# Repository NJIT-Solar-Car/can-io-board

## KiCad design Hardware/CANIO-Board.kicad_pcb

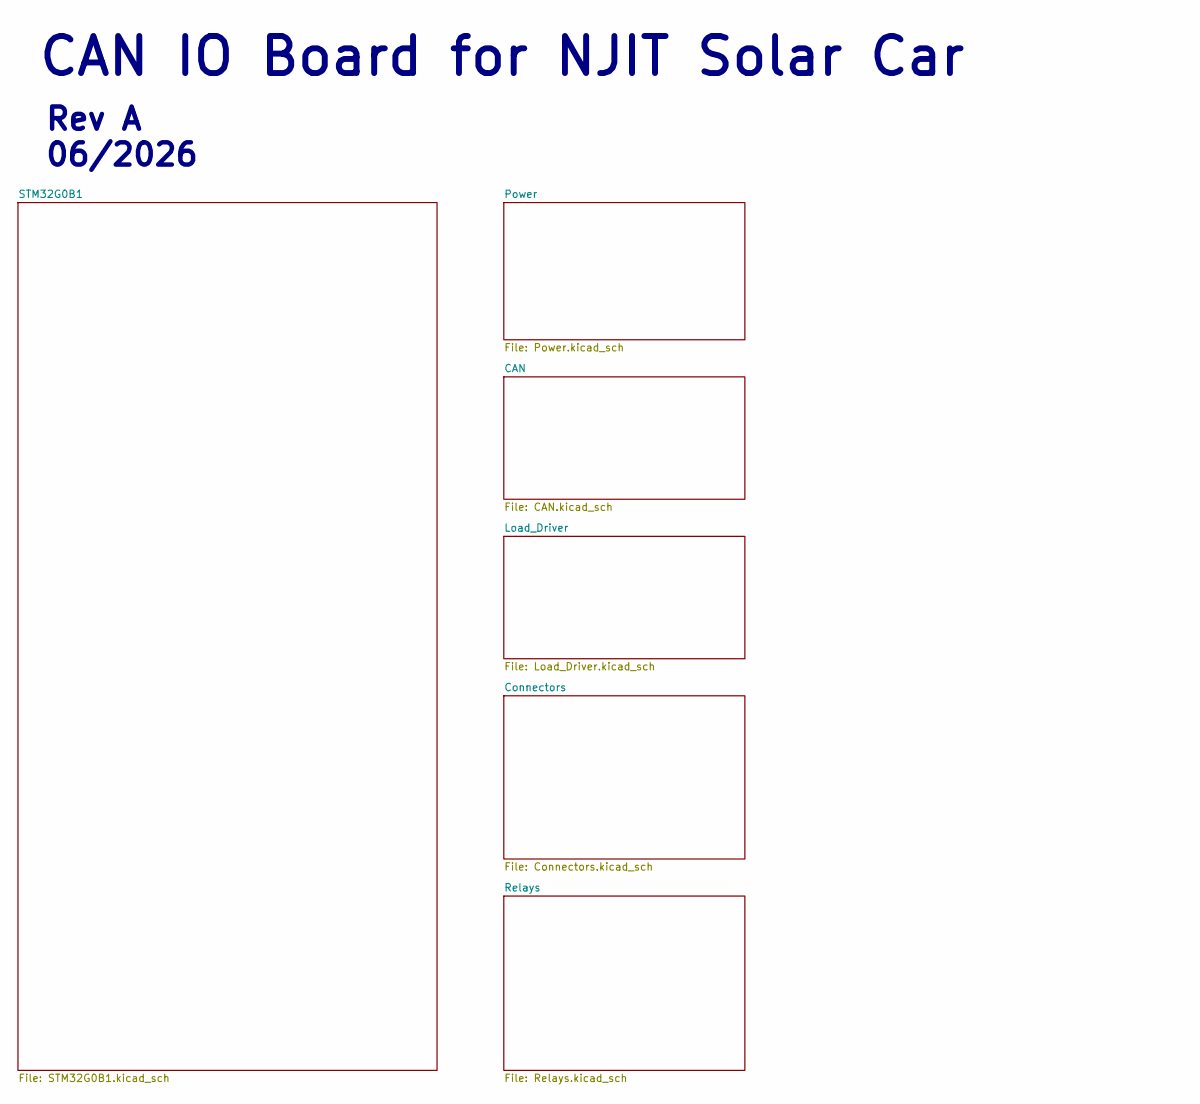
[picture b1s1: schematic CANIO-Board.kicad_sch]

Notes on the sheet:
CAN IO Board for NJIT Solar Car
Rev A 06/2026

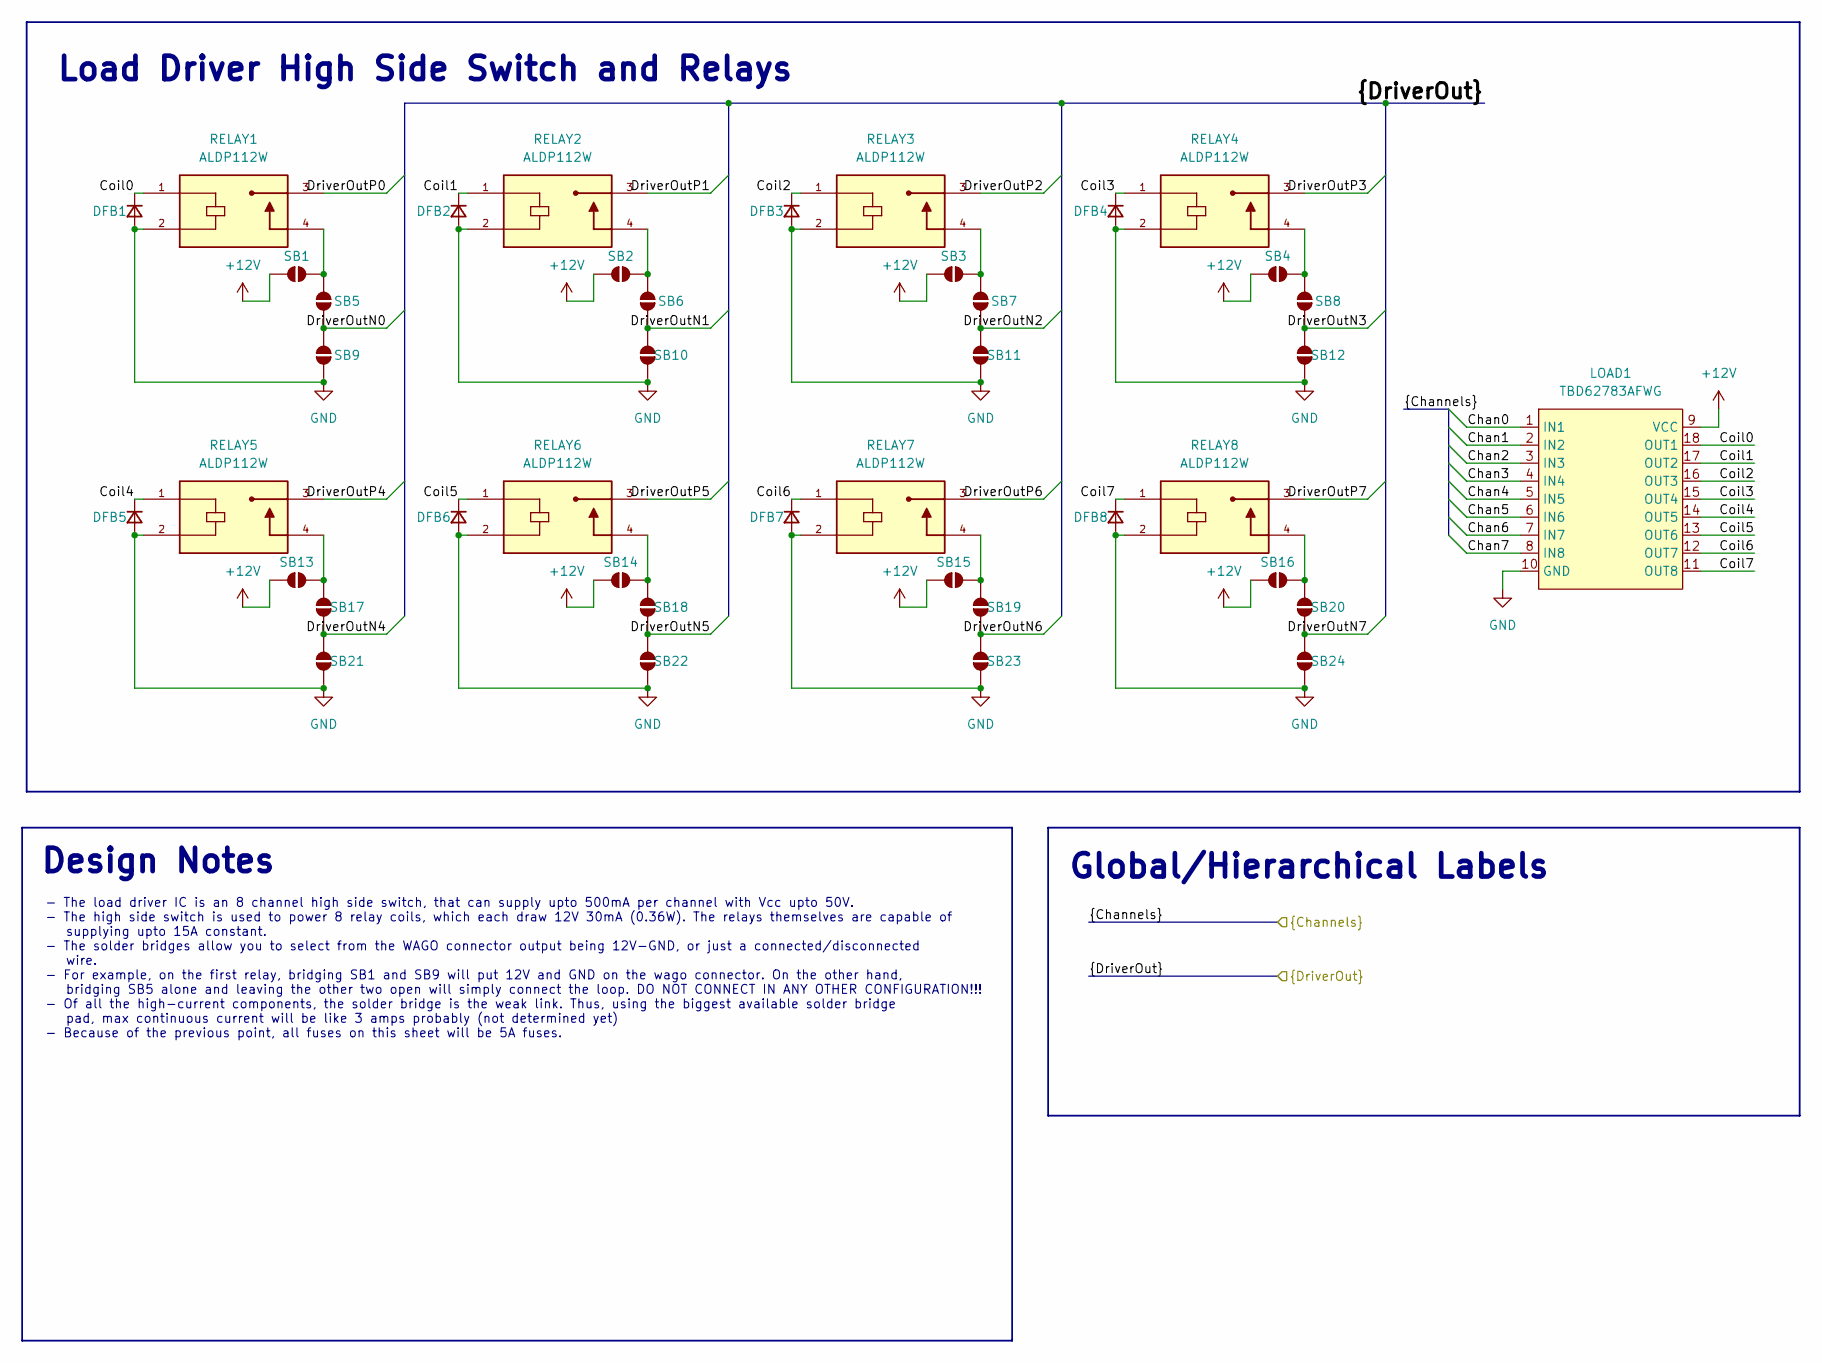
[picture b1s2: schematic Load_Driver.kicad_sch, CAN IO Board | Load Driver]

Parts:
DFB1, DFB2, DFB3, DFB4, DFB5, DFB6, DFB7, DFB8: D_Small; D_DO-35_SOD27_P7.62mm_Horizontal
LOAD1: TBD62783AFWG; SOP-18_7x12.5mm_P1.27mm
RELAY1, RELAY2, RELAY3, RELAY4, RELAY5, RELAY6, RELAY7, RELAY8: ALDP112W; RELAY_ALDP112W; PARTREV 2024.10
SB1, SB2, SB3, SB4, SB5, SB6, SB7, SB8, SB9, SB10, SB11, SB12, SB13, SB14, SB15, SB16, SB17, SB18, SB19, SB20, SB21, SB22, SB23, SB24: SolderJumper_2_Open; SolderJumper-2_P1.3mm_Open_TrianglePad1.0x1.5mm

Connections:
+12V: LOAD1.9 (VCC), SB1.1 (A), SB2.1 (A), SB3.1 (A), SB4.1 (A), SB13.1 (A), SB14.1 (A), SB15.1 (A), SB16.1 (A); also elsewhere on the board
/Connectors/DriverOutN0: SB5.2 (B), SB9.1 (A); also elsewhere on the board
/Connectors/DriverOutN1: SB6.2 (B), SB10.1 (A); also elsewhere on the board
/Connectors/DriverOutN2: SB7.2 (B), SB11.1 (A); also elsewhere on the board
/Connectors/DriverOutN3: SB8.2 (B), SB12.1 (A); also elsewhere on the board
/Connectors/DriverOutN4: SB17.2 (B), SB21.1 (A); also elsewhere on the board
/Connectors/DriverOutN5: SB18.2 (B), SB22.1 (A); also elsewhere on the board
/Connectors/DriverOutN6: SB19.2 (B), SB23.1 (A); also elsewhere on the board
/Connectors/DriverOutN7: SB20.2 (B), SB24.1 (A); also elsewhere on the board
/Connectors/DriverOutP0: RELAY1.3; also elsewhere on the board
/Connectors/DriverOutP1: RELAY2.3; also elsewhere on the board
/Connectors/DriverOutP2: RELAY3.3; also elsewhere on the board
/Connectors/DriverOutP3: RELAY4.3; also elsewhere on the board
/Connectors/DriverOutP4: RELAY5.3; also elsewhere on the board
/Connectors/DriverOutP5: RELAY6.3; also elsewhere on the board
/Connectors/DriverOutP6: RELAY7.3; also elsewhere on the board
/Connectors/DriverOutP7: RELAY8.3; also elsewhere on the board
/Load_Driver/Chan0: LOAD1.1 (IN1); also elsewhere on the board
/Load_Driver/Chan1: LOAD1.2 (IN2); also elsewhere on the board
/Load_Driver/Chan2: LOAD1.3 (IN3); also elsewhere on the board
/Load_Driver/Chan3: LOAD1.4 (IN4); also elsewhere on the board
/Load_Driver/Chan4: LOAD1.5 (IN5); also elsewhere on the board
/Load_Driver/Chan5: LOAD1.6 (IN6); also elsewhere on the board
/Load_Driver/Chan6: LOAD1.7 (IN7); also elsewhere on the board
/Load_Driver/Chan7: LOAD1.8 (IN8); also elsewhere on the board
/Load_Driver/Coil0: DFB1.1 (K), LOAD1.18 (OUT1), RELAY1.1
/Load_Driver/Coil1: DFB2.1 (K), LOAD1.17 (OUT2), RELAY2.1
/Load_Driver/Coil2: DFB3.1 (K), LOAD1.16 (OUT3), RELAY3.1
/Load_Driver/Coil3: DFB4.1 (K), LOAD1.15 (OUT4), RELAY4.1
/Load_Driver/Coil4: DFB5.1 (K), LOAD1.14 (OUT5), RELAY5.1
/Load_Driver/Coil5: DFB6.1 (K), LOAD1.13 (OUT6), RELAY6.1
/Load_Driver/Coil6: DFB7.1 (K), LOAD1.12 (OUT7), RELAY7.1
/Load_Driver/Coil7: DFB8.1 (K), LOAD1.11 (OUT8), RELAY8.1
GND: DFB1.2 (A), DFB2.2 (A), DFB3.2 (A), DFB4.2 (A), DFB5.2 (A), DFB6.2 (A), DFB7.2 (A), DFB8.2 (A), LOAD1.10 (GND), RELAY1.2, RELAY2.2, RELAY3.2, RELAY4.2, RELAY5.2, RELAY6.2, RELAY7.2, RELAY8.2, SB9.2 (B), SB10.2 (B), SB11.2 (B), SB12.2 (B), SB21.2 (B), SB22.2 (B), SB23.2 (B), SB24.2 (B); also elsewhere on the board
unnamed: RELAY1.4, SB1.2 (B), SB5.1 (A)
unnamed: RELAY2.4, SB2.2 (B), SB6.1 (A)
unnamed: RELAY3.4, SB3.2 (B), SB7.1 (A)
unnamed: RELAY4.4, SB4.2 (B), SB8.1 (A)
unnamed: RELAY5.4, SB13.2 (B), SB17.1 (A)
unnamed: RELAY6.4, SB14.2 (B), SB18.1 (A)
unnamed: RELAY7.4, SB15.2 (B), SB19.1 (A)
unnamed: RELAY8.4, SB16.2 (B), SB20.1 (A)

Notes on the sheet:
Design Notes
Load Driver High Side Switch and Relays
- The load driver IC is an 8 channel high side switch, that can supply upto 500mA per channel with Vcc upto 50V. - The high side switch is used to power 8 relay coils, which each draw 12V 30mA (0.36W). The relays themselves are capable of supplying upto 15A constant. - The solder bridges allow you 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
Global/Hierarchical Labels

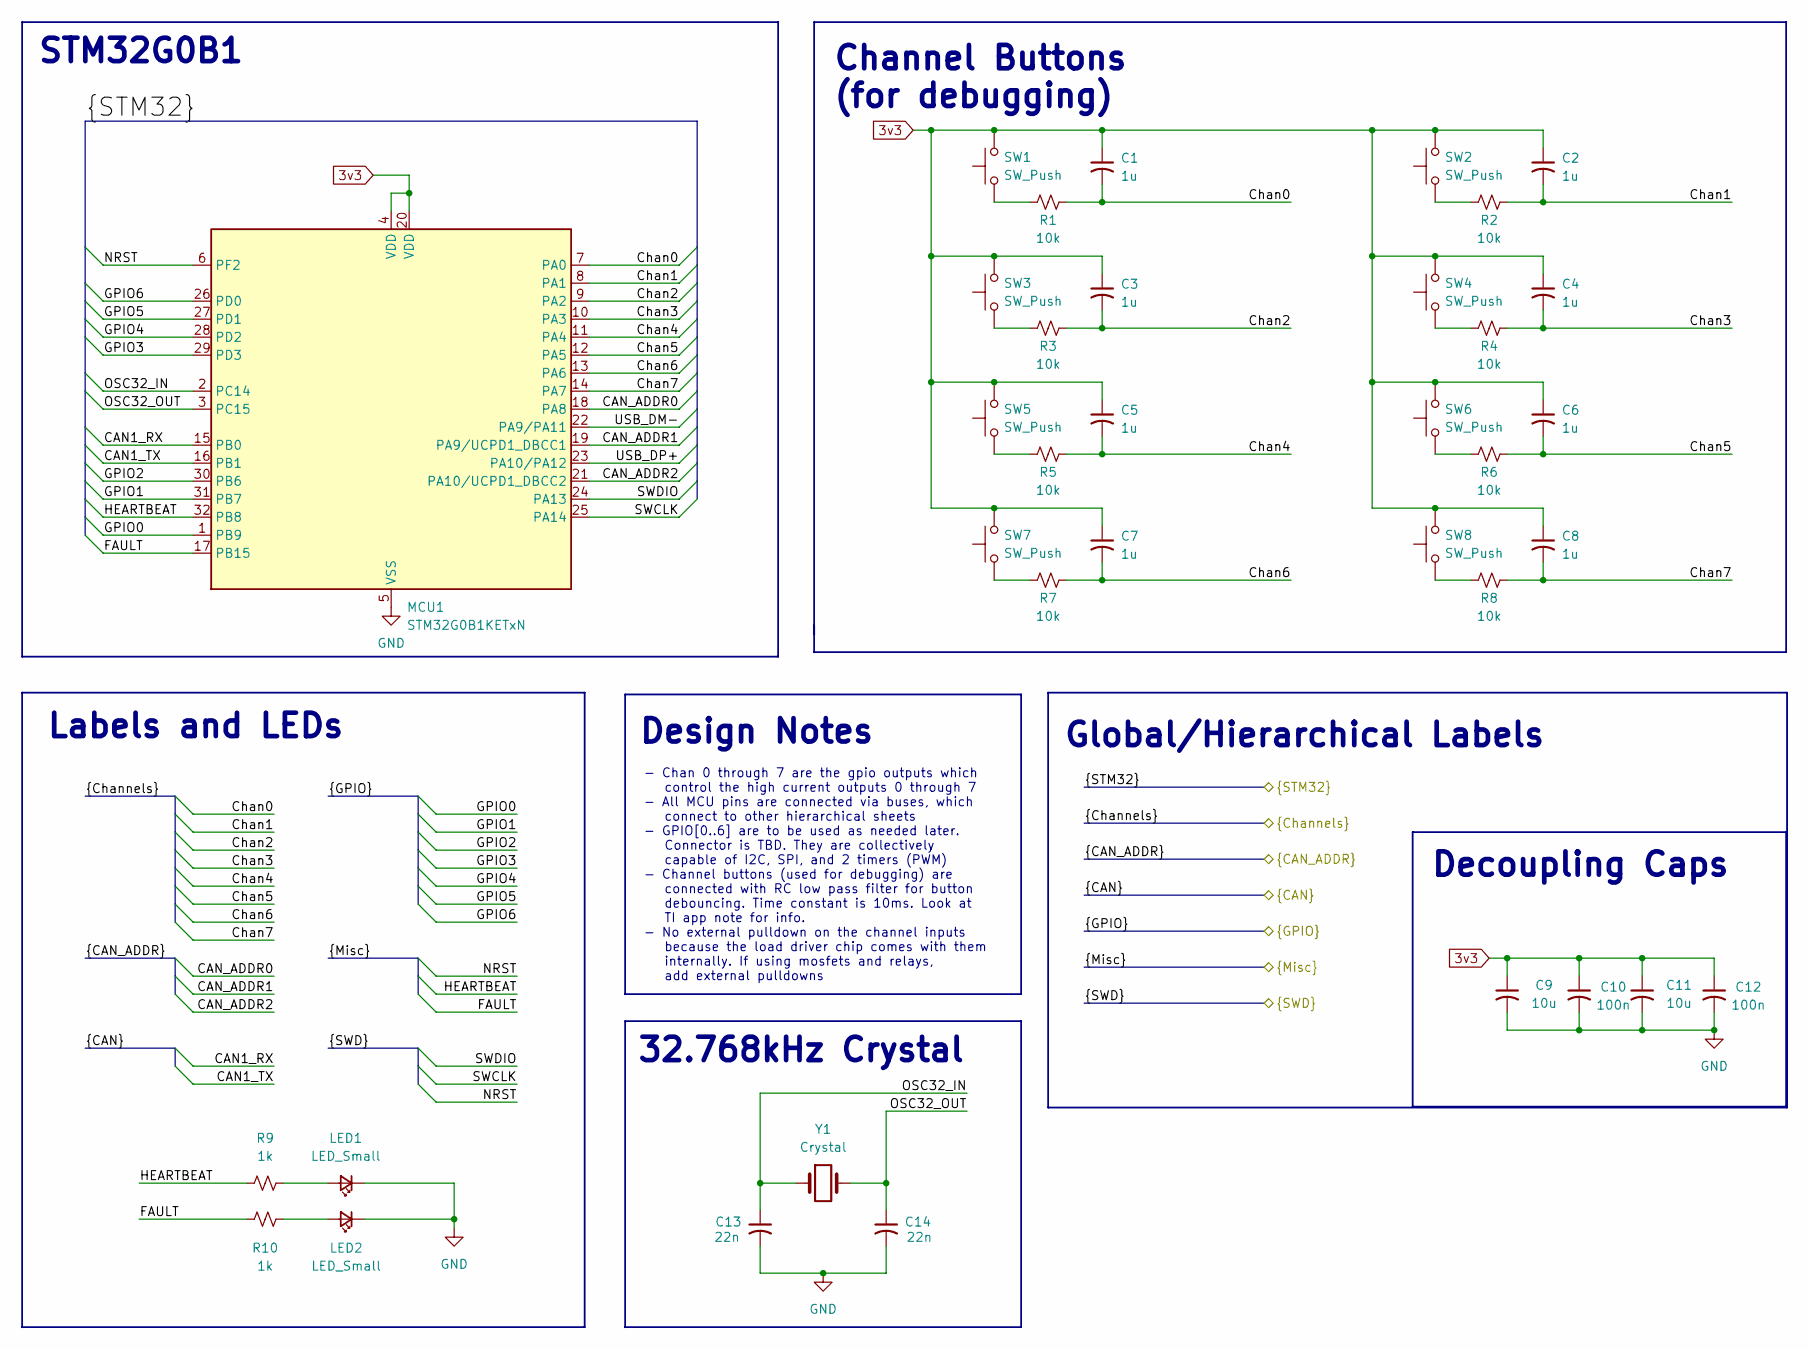
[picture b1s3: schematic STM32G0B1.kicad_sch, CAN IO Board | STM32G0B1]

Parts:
C1, C2, C3, C4, C5, C6, C7, C8: 1u; C_0603_1608Metric_Pad1.08x0.95mm_HandSolder
C9, C11: 10u; C_0603_1608Metric_Pad1.08x0.95mm_HandSolder
C10, C12: 100n; C_0603_1608Metric_Pad1.08x0.95mm_HandSolder
C13, C14: 22n; C_0603_1608Metric_Pad1.08x0.95mm_HandSolder
LED1, LED2: LED_Small; LED_1206_3216Metric_Pad1.42x1.75mm_HandSolder
MCU1: STM32G0B1KETxN; LQFP-32_7x7mm_P0.8mm
R1, R2, R3, R4, R5, R6, R7, R8: 10k; R_0603_1608Metric_Pad0.98x0.95mm_HandSolder
R9, R10: 1k; R_0603_1608Metric_Pad0.98x0.95mm_HandSolder
SW1, SW2, SW3, SW4, SW5, SW6, SW7, SW8: SW_Push; SW_Push_1P1T_NO_CK_KSC7xxJ
Y1: Crystal; Crystal_SMD_3215-2Pin_3.2x1.5mm

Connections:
3v3: C1.1, C2.1, C3.1, C4.1, C5.1, C6.1, C7.1, C8.1, C9.1, C10.1, C11.1, C12.1, MCU1.4 (VDD), MCU1.20 (VDD), SW1.2, SW2.2, SW3.2, SW4.2, SW5.2, SW6.2, SW7.2, SW8.2; also elsewhere on the board
/CAN/CAN1_RX: MCU1.15 (PB0); also elsewhere on the board
/CAN/CAN1_TX: MCU1.16 (PB1); also elsewhere on the board
/Connectors/CAN_ADDR0: MCU1.18 (PA8); also elsewhere on the board
/Connectors/CAN_ADDR1: MCU1.19 (PA9/UCPD1_DBCC1); also elsewhere on the board
/Connectors/CAN_ADDR2: MCU1.21 (PA10/UCPD1_DBCC2); also elsewhere on the board
/Connectors/FAULT: MCU1.17 (PB15), R10.1
/Connectors/GPIO0: MCU1.1 (PB9); also elsewhere on the board
/Connectors/GPIO1: MCU1.31 (PB7); also elsewhere on the board
/Connectors/GPIO2: MCU1.30 (PB6); also elsewhere on the board
/Connectors/GPIO3: MCU1.29 (PD3); also elsewhere on the board
/Connectors/GPIO4: MCU1.28 (PD2); also elsewhere on the board
/Connectors/GPIO5: MCU1.27 (PD1); also elsewhere on the board
/Connectors/GPIO6: MCU1.26 (PD0); also elsewhere on the board
/Connectors/HEARTBEAT: MCU1.32 (PB8), R9.1
/Connectors/NRST: MCU1.6 (PF2); also elsewhere on the board
/Connectors/OSC32_IN: C13.1, MCU1.2 (PC14), Y1.1
/Connectors/OSC32_OUT: C14.1, MCU1.3 (PC15), Y1.2
/Connectors/SWCLK: MCU1.25 (PA14); also elsewhere on the board
/Connectors/SWDIO: MCU1.24 (PA13); also elsewhere on the board
/Connectors/USB_DM-: MCU1.22 (PA9/PA11); also elsewhere on the board
/Connectors/USB_DP+: MCU1.23 (PA10/PA12); also elsewhere on the board
/Load_Driver/Chan0: C1.2, MCU1.7 (PA0), R1.1; also elsewhere on the board
/Load_Driver/Chan1: C2.2, MCU1.8 (PA1), R2.1; also elsewhere on the board
/Load_Driver/Chan2: C3.2, MCU1.9 (PA2), R3.1; also elsewhere on the board
/Load_Driver/Chan3: C4.2, MCU1.10 (PA3), R4.1; also elsewhere on the board
/Load_Driver/Chan4: C5.2, MCU1.11 (PA4), R5.1; also elsewhere on the board
/Load_Driver/Chan5: C6.2, MCU1.12 (PA5), R6.1; also elsewhere on the board
/Load_Driver/Chan6: C7.2, MCU1.13 (PA6), R7.1; also elsewhere on the board
/Load_Driver/Chan7: C8.2, MCU1.14 (PA7), R8.1; also elsewhere on the board
GND: C9.2, C10.2, C11.2, C12.2, C13.2, C14.2, LED1.1 (K), LED2.1 (K), MCU1.5 (VSS); also elsewhere on the board
unnamed: LED1.2 (A), R9.2
unnamed: LED2.2 (A), R10.2
unnamed: R1.2, SW1.1
unnamed: R2.2, SW2.1
unnamed: R3.2, SW3.1
unnamed: R4.2, SW4.1
unnamed: R5.2, SW5.1
unnamed: R6.2, SW6.1
unnamed: R7.2, SW7.1
unnamed: R8.2, SW8.1

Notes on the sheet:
Labels and LEDs
32.768kHz Crystal
Channel Buttons (for debugging)
STM32G0B1
- Chan 0 through 7 are the gpio outputs which control the high current outputs 0 through 7 - All MCU pins are connected via buses, which connect to other hierarchical sheets - GPIO[0..6] are to be used as needed later. Connector is TBD. They are collectively capable of I2C, SPI, and 2 timers (PWM) 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
Global/Hierarchical Labels
Decoupling Caps
Design Notes

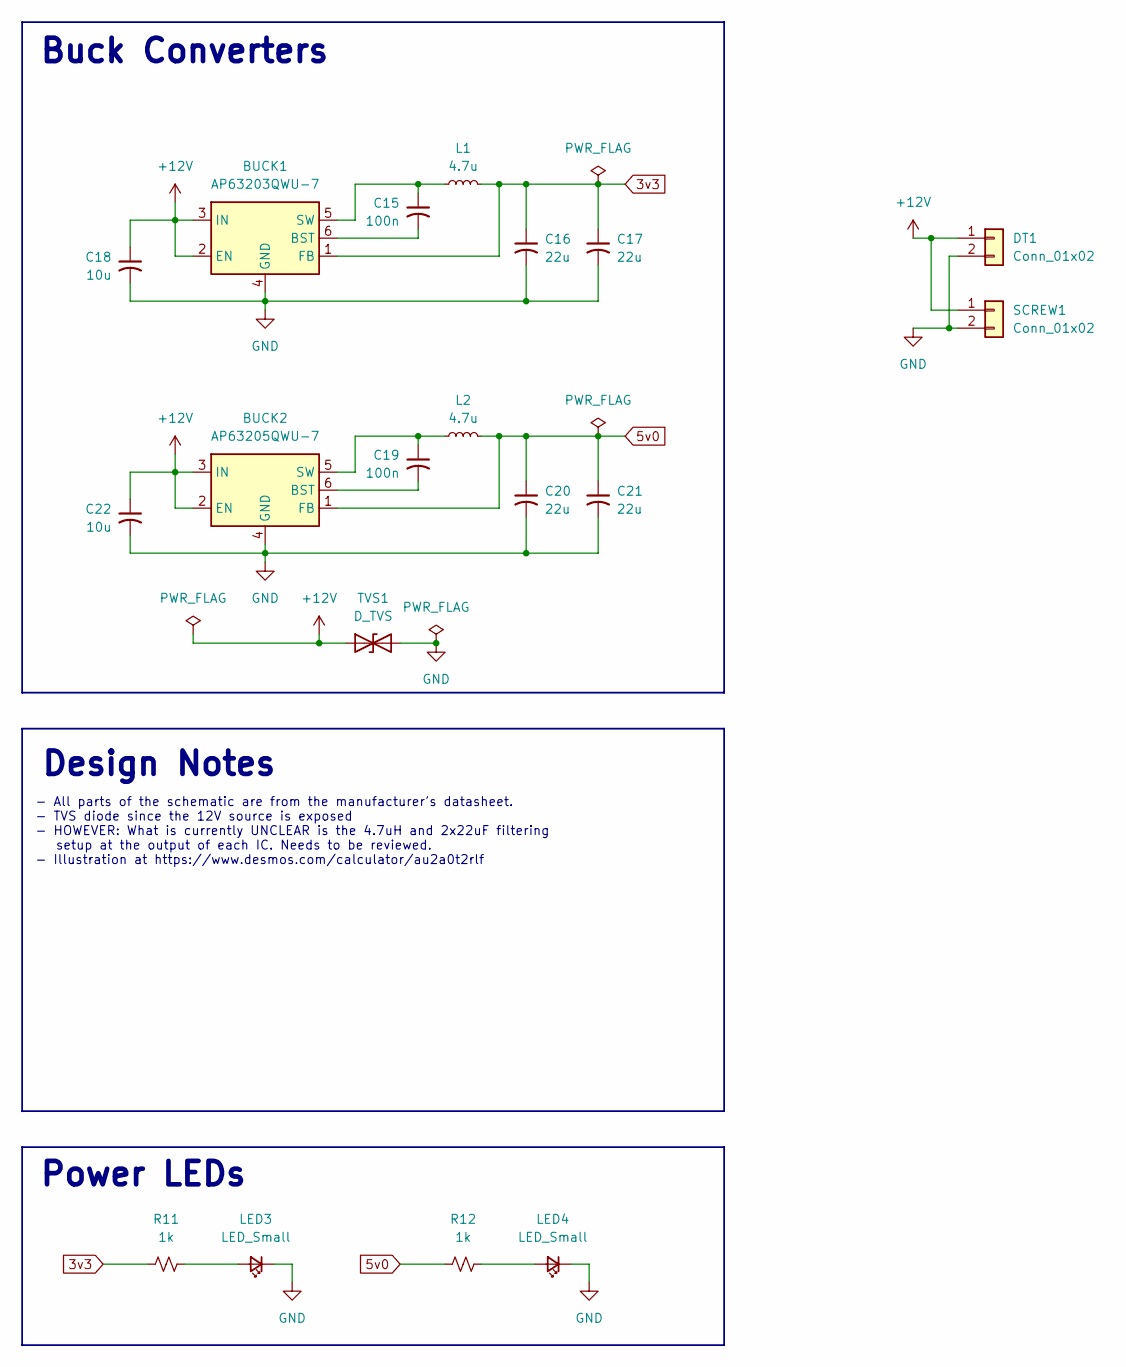
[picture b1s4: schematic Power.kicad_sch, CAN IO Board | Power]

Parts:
BUCK1: AP63203QWU-7; TSOT-23-6
BUCK2: AP63205QWU-7; TSOT-23-6
C15, C19: 100n; C_0603_1608Metric_Pad1.08x0.95mm_HandSolder
C16, C17, C20, C21: 22u; CP_Elec_4x4.5
C18, C22: 10u; C_0603_1608Metric_Pad1.08x0.95mm_HandSolder
DT1: Conn_01x02; TE_DTF13-2P
L1, L2: 4.7u; L_Axial_L7.0mm_D3.3mm_P5.08mm_Vertical_Fastron_MICC
LED3, LED4: LED_Small; LED_1206_3216Metric_Pad1.42x1.75mm_HandSolder
R11, R12: 1k; R_0603_1608Metric_Pad0.98x0.95mm_HandSolder
SCREW1: Conn_01x02; TerminalBlock_MaiXu_MX126-5.0-02P_1x02_P5.00mm
TVS1: D_TVS; D_SMA_Handsoldering

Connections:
3v3: BUCK1.1 (FB), C16.1, C17.1, L1.2, R11.1; also elsewhere on the board
5v0: BUCK2.1 (FB), C20.1, C21.1, L2.2, R12.1; also elsewhere on the board
+12V: BUCK1.2 (EN), BUCK1.3 (IN), BUCK2.2 (EN), BUCK2.3 (IN), C18.1, C22.1, DT1.1, SCREW1.1, TVS1.1 (A1); also elsewhere on the board
GND: BUCK1.4 (GND), BUCK2.4 (GND), C16.2, C17.2, C18.2, C20.2, C21.2, C22.2, DT1.2, LED3.1 (K), LED4.1 (K), SCREW1.2, TVS1.2 (A2); also elsewhere on the board
unnamed: BUCK1.6 (BST), C15.2
unnamed: BUCK1.5 (SW), C15.1, L1.1
unnamed: BUCK2.6 (BST), C19.2
unnamed: BUCK2.5 (SW), C19.1, L2.1
unnamed: LED3.2 (A), R11.2
unnamed: LED4.2 (A), R12.2

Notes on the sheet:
- All parts of the schematic are from the manufacturer's datasheet. - TVS diode since the 12V source is exposed - HOWEVER: What is currently UNCLEAR is the 4.7uH and 2x22uF filtering setup at the output of each IC. Needs to be reviewed. - Illustration at https://www.desmos.com/calculator/au2a0t2rlf
Buck Converters
Power LEDs
Design Notes

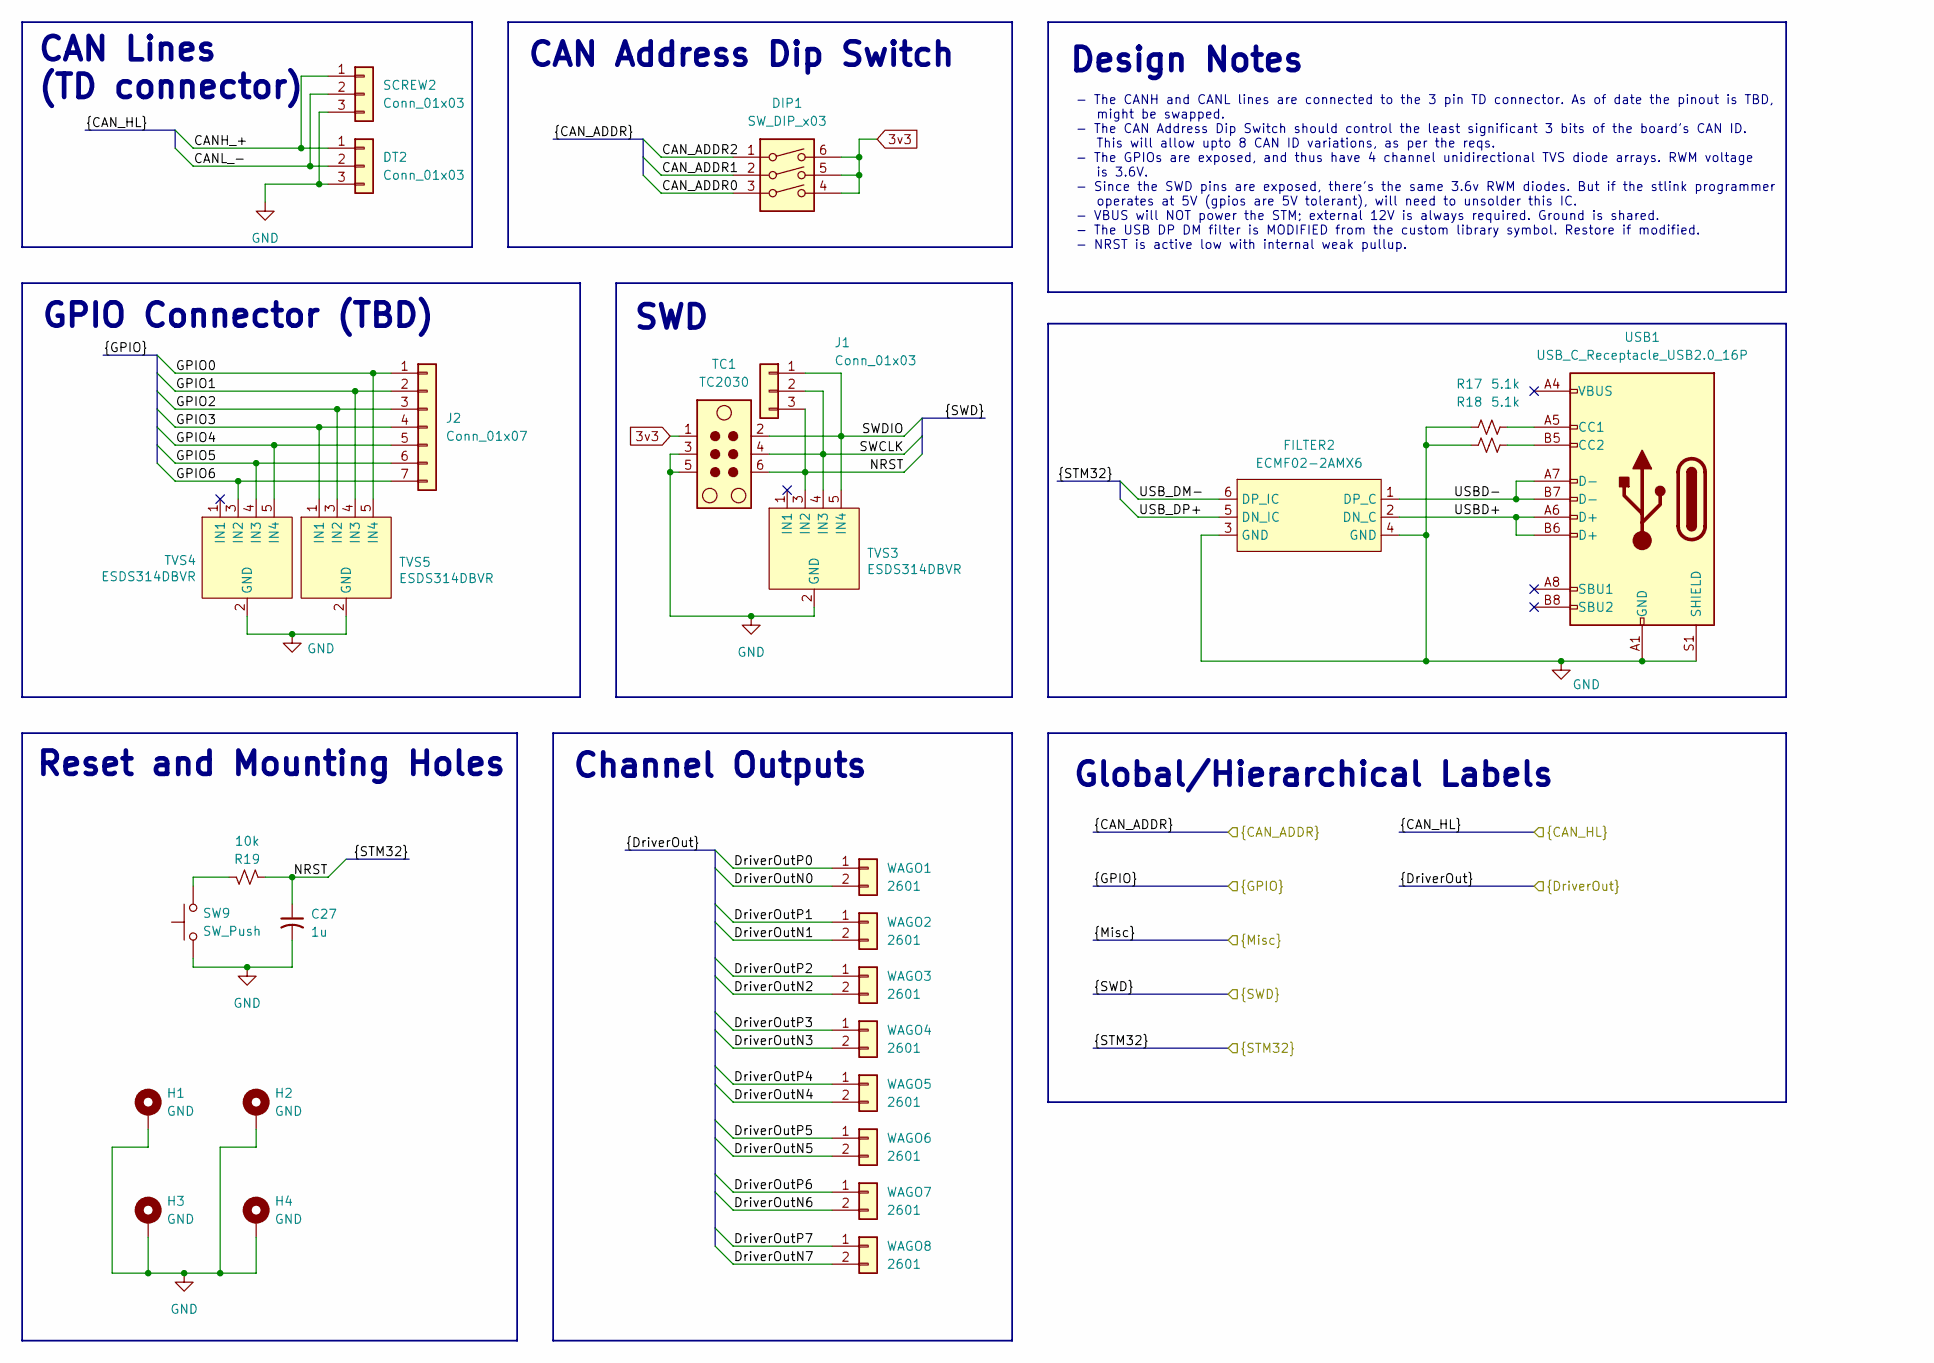
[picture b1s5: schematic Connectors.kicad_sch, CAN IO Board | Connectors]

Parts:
C27: 1u; C_0603_1608Metric_Pad1.08x0.95mm_HandSolder
DIP1: SW_DIP_x03; SW_DIP_SPSTx03_Slide_9.78x9.8mm_W7.62mm_P2.54mm
DT2: Conn_01x03; TE_DTF13-3P
FILTER2: ECMF02-2AMX6; ECMF02-2AMX6_QFN-6L
H1, H2, H3, H4: GND; MountingHole_3.5mm_Pad_Via
J1: Conn_01x03; PinHeader_1x03_P2.54mm_Vertical
J2: Conn_01x07; PinHeader_1x07_P2.54mm_Vertical
R17, R18: 5.1k; R_0603_1608Metric_Pad0.98x0.95mm_HandSolder
R19: 10k; R_0603_1608Metric_Pad0.98x0.95mm_HandSolder
SCREW2: Conn_01x03; TerminalBlock_MaiXu_MX126-5.0-03P_1x03_P5.00mm
SW9: SW_Push; SW_Push_1P1T_NO_CK_KSC7xxJ
TC1: TC2030; Tag-Connect_TC2030-IDC-NL_2x03_P1.27mm_Vertical
TVS3, TVS4, TVS5: ESDS314DBVR; SOT-23-5
USB1: USB_C_Receptacle_USB2.0_16P; SHOUHAN_TYPE-C_16PIN_2MD__073_
WAGO1, WAGO2, WAGO3, WAGO4, WAGO5, WAGO6, WAGO7, WAGO8: 2601; TerminalBlock_WAGO_2601-1102_1x02_P3.50mm_Horizontal

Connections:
3v3: DIP1.4, DIP1.5, DIP1.6, TC1.1; also elsewhere on the board
/CAN/CANH_+: DT2.1, SCREW2.1; also elsewhere on the board
/CAN/CANL_-: DT2.2, SCREW2.2; also elsewhere on the board
/Connectors/CAN_ADDR0: DIP1.3; also elsewhere on the board
/Connectors/CAN_ADDR1: DIP1.2; also elsewhere on the board
/Connectors/CAN_ADDR2: DIP1.1; also elsewhere on the board
/Connectors/DriverOutN0: WAGO1.2; also elsewhere on the board
/Connectors/DriverOutN1: WAGO2.2; also elsewhere on the board
/Connectors/DriverOutN2: WAGO3.2; also elsewhere on the board
/Connectors/DriverOutN3: WAGO4.2; also elsewhere on the board
/Connectors/DriverOutN4: WAGO5.2; also elsewhere on the board
/Connectors/DriverOutN5: WAGO6.2; also elsewhere on the board
/Connectors/DriverOutN6: WAGO7.2; also elsewhere on the board
/Connectors/DriverOutN7: WAGO8.2; also elsewhere on the board
/Connectors/DriverOutP0: WAGO1.1; also elsewhere on the board
/Connectors/DriverOutP1: WAGO2.1; also elsewhere on the board
/Connectors/DriverOutP2: WAGO3.1; also elsewhere on the board
/Connectors/DriverOutP3: WAGO4.1; also elsewhere on the board
/Connectors/DriverOutP4: WAGO5.1; also elsewhere on the board
/Connectors/DriverOutP5: WAGO6.1; also elsewhere on the board
/Connectors/DriverOutP6: WAGO7.1; also elsewhere on the board
/Connectors/DriverOutP7: WAGO8.1; also elsewhere on the board
/Connectors/GPIO0: J2.1, TVS5.5 (IN4); also elsewhere on the board
/Connectors/GPIO1: J2.2, TVS5.4 (IN3); also elsewhere on the board
/Connectors/GPIO2: J2.3, TVS5.3 (IN2); also elsewhere on the board
/Connectors/GPIO3: J2.4, TVS5.1 (IN1); also elsewhere on the board
/Connectors/GPIO4: J2.5, TVS4.5 (IN4); also elsewhere on the board
/Connectors/GPIO5: J2.6, TVS4.4 (IN3); also elsewhere on the board
/Connectors/GPIO6: J2.7, TVS4.3 (IN2); also elsewhere on the board
/Connectors/NRST: C27.1, J1.3, R19.1, TC1.6, TVS3.3 (IN2); also elsewhere on the board
/Connectors/SWCLK: J1.2, TC1.4, TVS3.4 (IN3); also elsewhere on the board
/Connectors/SWDIO: J1.1, TC1.2, TVS3.5 (IN4); also elsewhere on the board
/Connectors/USBD+: FILTER2.2 (DN_C), USB1.A6 (D+), USB1.B6 (D+)
/Connectors/USBD-: FILTER2.1 (DP_C), USB1.A7 (D-), USB1.B7 (D-)
/Connectors/USB_DM-: FILTER2.6 (DP_IC); also elsewhere on the board
/Connectors/USB_DP+: FILTER2.5 (DN_IC); also elsewhere on the board
GND: C27.2, DT2.3, FILTER2.3 (GND), FILTER2.4 (GND), H1.1, H2.1, H3.1, H4.1, R17.1, R18.1, SCREW2.3, SW9.1, TC1.3, TC1.5, TVS3.2 (GND), TVS4.2 (GND), TVS5.2 (GND), USB1.A1 (GND), USB1.A12 (GND), USB1.B1 (GND), USB1.B12 (GND), USB1.S1 (SHIELD); also elsewhere on the board
unnamed: R19.2, SW9.2
unnamed: R17.2, USB1.A5 (CC1)
unnamed: R18.2, USB1.B5 (CC2)

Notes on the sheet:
CAN Lines (TD connector)
CAN Address Dip Switch
SWD
Reset and Mounting Holes
- The CANH and CANL lines are connected to the 3 pin TD connector. As of date the pinout is TBD, might be swapped. - The CAN Address Dip Switch should control the least significant 3 bits of the board's CAN ID. This will allow upto 8 CAN ID variations, as per the reqs. - The GPIOs are exposed, and 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
Channel Outputs
Global/Hierarchical Labels
Design Notes
GPIO Connector (TBD)

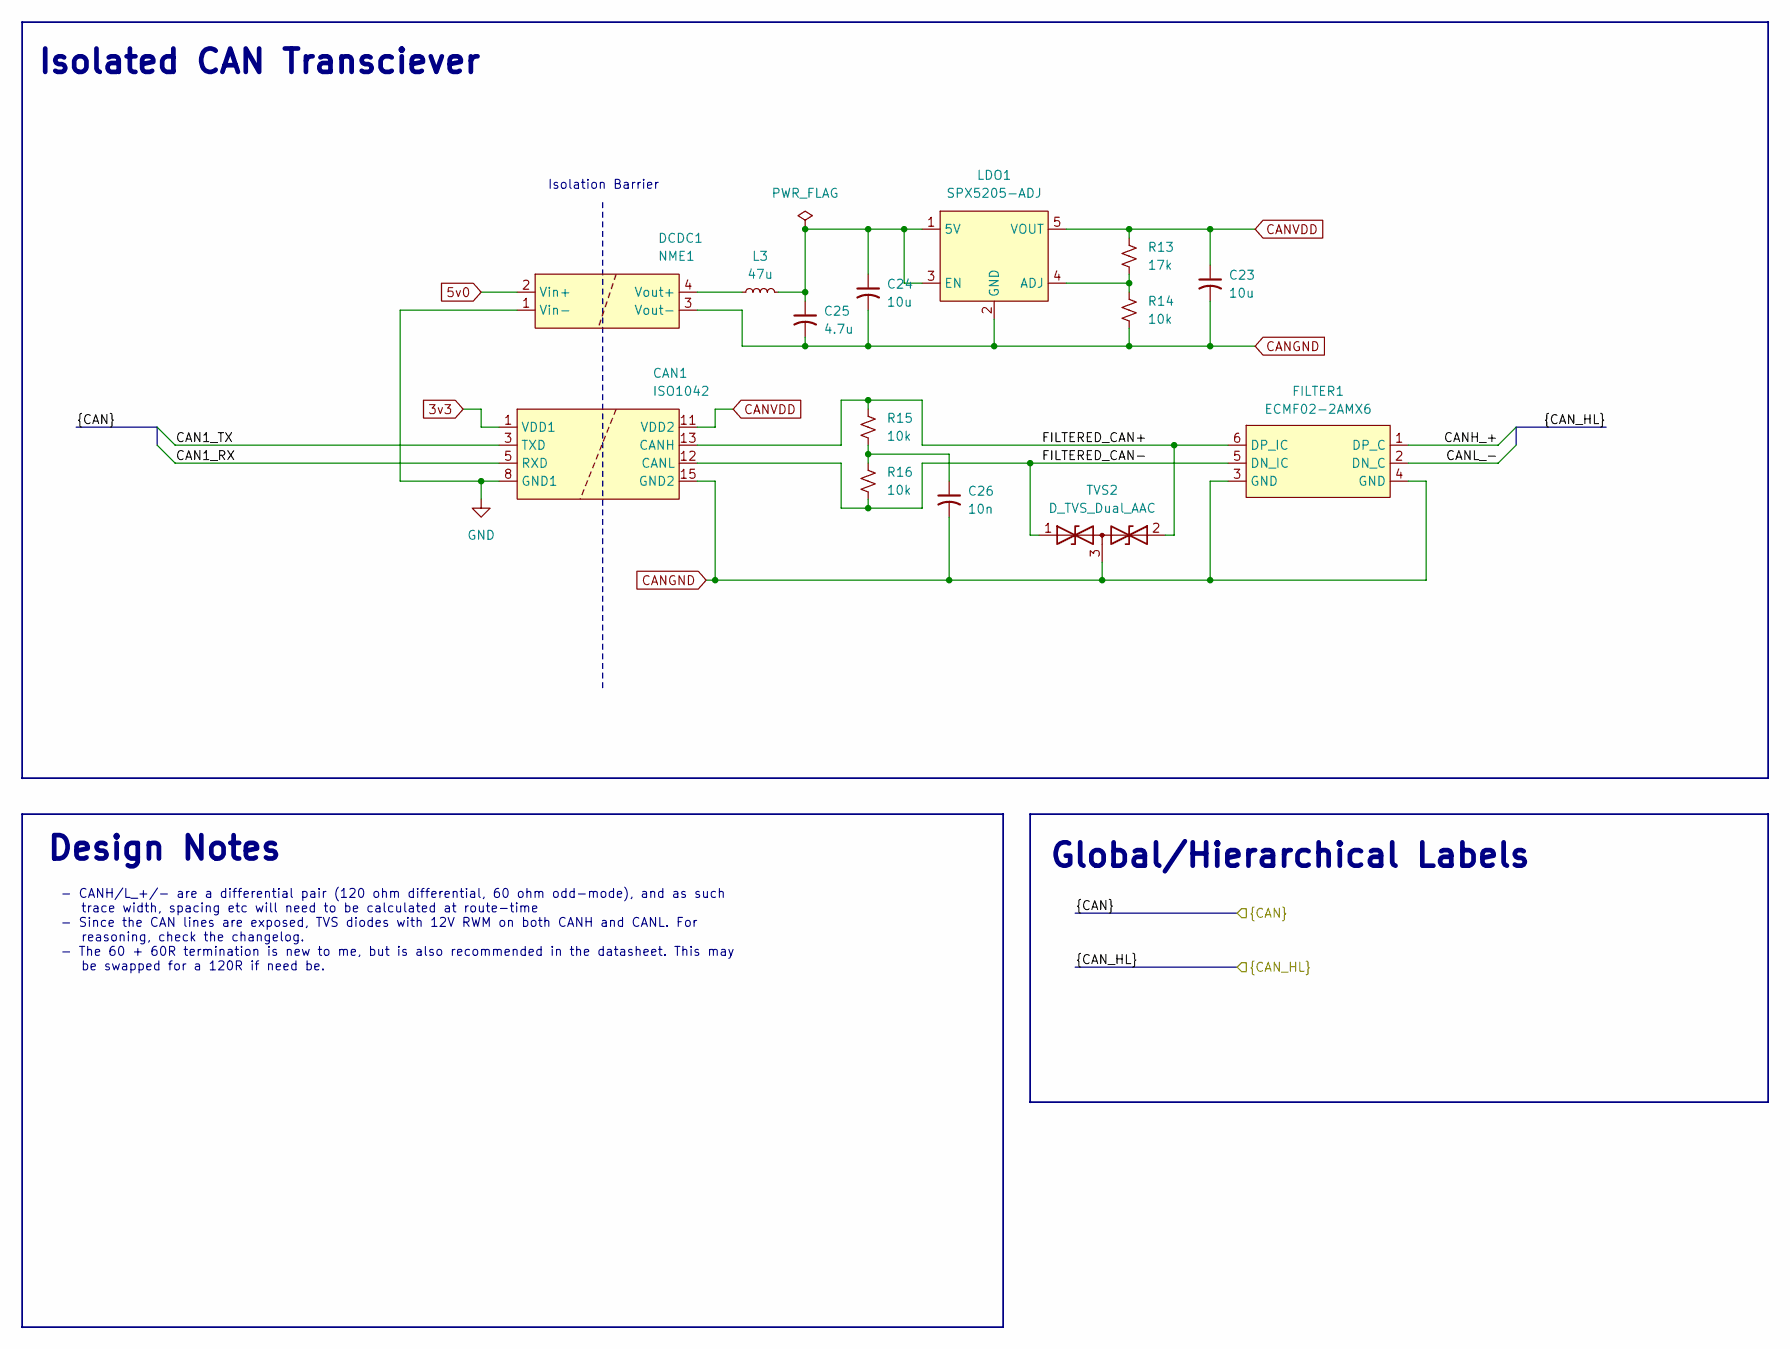
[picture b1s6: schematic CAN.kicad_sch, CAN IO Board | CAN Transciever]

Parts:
C23, C24: 10u; C_0603_1608Metric_Pad1.08x0.95mm_HandSolder
C25: 4.7u; C_0603_1608Metric_Pad1.08x0.95mm_HandSolder
C26: 10n; C_0603_1608Metric_Pad1.08x0.95mm_HandSolder
CAN1: ISO1042; SOIC-16W_7.5x10.3mm_P1.27mm
DCDC1: NME1; NME1S
FILTER1: ECMF02-2AMX6; ECMF02-2AMX6_QFN-6L
L3: 47u; L_Axial_L7.0mm_D3.3mm_P5.08mm_Vertical_Fastron_MICC
LDO1: SPX5205-ADJ; SOT-23-5_HandSoldering
R13: 17k; R_0603_1608Metric_Pad0.98x0.95mm_HandSolder
R14, R15, R16: 10k; R_0603_1608Metric_Pad0.98x0.95mm_HandSolder
TVS2: D_TVS_Dual_AAC; SOT-23

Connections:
3v3: CAN1.1 (VDD1); also elsewhere on the board
5v0: DCDC1.2 (Vin+); also elsewhere on the board
/CAN/CAN1_RX: CAN1.5 (RXD); also elsewhere on the board
/CAN/CAN1_TX: CAN1.3 (TXD); also elsewhere on the board
/CAN/CANH_+: FILTER1.1 (DP_C); also elsewhere on the board
/CAN/CANL_-: FILTER1.2 (DN_C); also elsewhere on the board
/CAN/FILTERED_CAN+: CAN1.13 (CANH), FILTER1.6 (DP_IC), R15.1, TVS2.2 (A2)
/CAN/FILTERED_CAN-: CAN1.12 (CANL), FILTER1.5 (DN_IC), R16.2, TVS2.1 (A1)
CANGND: C23.2, C24.2, C25.2, C26.2, CAN1.9 (GND2), CAN1.10 (GND2), CAN1.15 (GND2), DCDC1.3 (Vout-), FILTER1.3 (GND), FILTER1.4 (GND), LDO1.2 (GND), R14.2, TVS2.3 (common)
CANVDD: C23.1, CAN1.11 (VDD2), CAN1.16 (VDD2), LDO1.5 (VOUT), R13.1
GND: CAN1.2 (GND1), CAN1.8 (GND1), DCDC1.1 (Vin-); also elsewhere on the board
unnamed: C26.1, R15.2, R16.1
unnamed: DCDC1.4 (Vout+), L3.1
unnamed: C24.1, C25.1, L3.2, LDO1.1 (5V), LDO1.3 (EN)
unnamed: LDO1.4 (ADJ), R13.2, R14.1

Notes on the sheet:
- CANH/L_+/- are a differential pair (120 ohm differential, 60 ohm odd-mode), and as such trace width, spacing etc will need to be calculated at route-time - Since the CAN lines are exposed, TVS diodes with 12V RWM on both CANH and CANL. For reasoning, check the changelog. - The 60 + 60R terminatio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
Isolation Barrier
Design Notes
Isolated CAN Transciever
Global/Hierarchical Labels

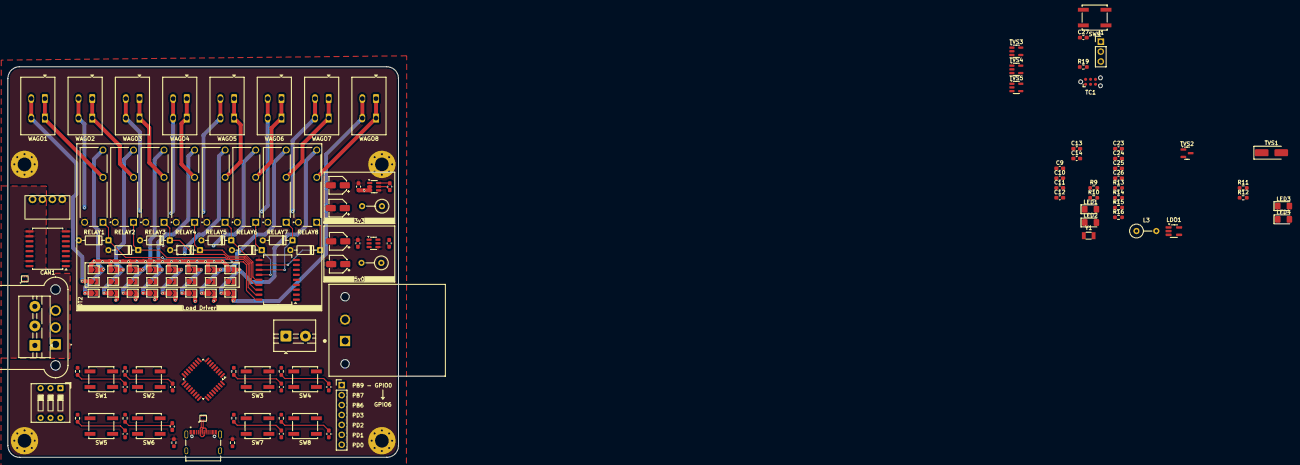
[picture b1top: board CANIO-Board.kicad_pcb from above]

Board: 4 copper layers, 100.0 x 100.0 mm, 138 parts (0 on the bottom side), 96 nets.

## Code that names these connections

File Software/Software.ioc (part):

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Mcu.Name=STM32G0B1K(B-C-E)Tx
Mcu.Package=LQFP32
Mcu.UserName=STM32G0B1KETx
PA0.Mode=SYS_WakeUp0
PA0.Signal=SYS_WKUP1
PA10.GPIOParameters=GPIO_Label
PA10.GPIO_Label=CAN_ADDR2
PA10.Signal=GPIO_Input
PA11\ [PA9].Mode=FDCAN_Activate
PA11\ [PA9].Signal=FDCAN1_RX
PA12\ [PA10].Mode=FDCAN_Activate
PA12\ [PA10].Signal=FDCAN1_TX
PA13.Mode=Serial_Wire
PA13.Signal=SYS_SWDIO
PA14-BOOT0.Mode=Serial_Wire
PA14-BOOT0.Signal=SYS_SWCLK
PA6.GPIOParameters=GPIO_Label
PA6.GPIO_Label=HEARTBEAT
PA6.Signal=GPIO_Output
PA7.GPIOParameters=GPIO_Label
PA7.GPIO_Label=FAULT
PA7.Signal=GPIO_Output
PA8.GPIOParameters=GPIO_Label
PA8.GPIO_Label=CAN_ADDR0
PA8.Signal=GPIO_Input
PA9.GPIOParameters=GPIO_Label
PA9.GPIO_Label=CAN_ADDR1
PA9.Signal=GPIO_Input
PB3.GPIOParameters=GPIO_Label
PB3.GPIO_Label=LowChan1
PB3.Signal=GPIO_Output
PB4.GPIOParameters=GPIO_Label
PB4.GPIO_Label=LowChan2
PB4.Signal=GPIO_Output
PB5.GPIOParameters=GPIO_Label
PB5.GPIO_Label=LowChan3
PB5.Signal=GPIO_Output
PB6.GPIOParameters=GPIO_Label
PB6.GPIO_Label=HighChan1
PB6.Signal=GPIO_Output
PB7.GPIOParameters=GPIO_Label
PB7.GPIO_Label=HighChan2
PB7.Signal=GPIO_Output
RCC.HSE_VALUE=8000000
RCC.SYSCLKFreq_VALUE=16000000
board=custom

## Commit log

2026-06-08 Added initial IOC and picture of configuration
2026-06-08 Finished the STM sheet mostly
    - Added a bus for the STM32, as well as the individual peripherals
    - Added LEDs for the Heartbeat and Fault outputs.
    - Added 5 pushbuttons for the 5 channels, along with button debouncing
    - Refer to TI's button debouncing AN. RC low pass w/ 10ms time
    constant. UNSURE if the schematic is correct, someone will
    have to check.
2026-06-08 Added the power schematic
    - Finished the power schematic.
    - HOWEVER, there is some confusion (Arnav) about the post-supply
    filtering. Needs to be reviewed before ordering.
2026-06-10 Fixed up the schematic a little, and did *most* footprint assigning
    - Most footprints are assigned. Ones that arent either don't exist, or
    are out of stock at digikey and are thus not work making/adding.
    - Details of next steps will be put into changelog soon
2026-06-10 updated the changelog
2026-06-11 Completed the PCB setup. Relevant calculations in the CHANGELOG.
2026-06-12 temp
